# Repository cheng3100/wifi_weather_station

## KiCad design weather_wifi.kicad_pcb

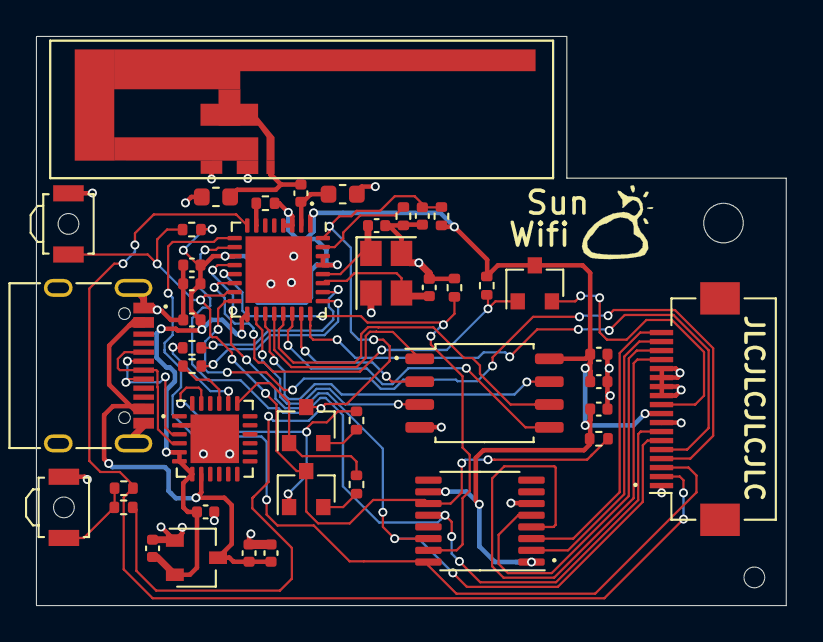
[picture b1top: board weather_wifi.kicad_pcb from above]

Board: 2 copper layers, 41.7 x 31.6 mm, 44 parts (0 on the bottom side), 41 nets.

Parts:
AE1: Antenna_pcb; antenna_trace_2.4g
C1, C5, C10, C13: 1uF; C_0402_1005Metric
C2, C3: 10pF; C_0402_1005Metric
C4: 10uF; C_0402_1005Metric
C6, C7, C8, C9, C11, C12: 0.1uF; C_0402_1005Metric
C14: 5.6pF; C_0402_1005Metric
G1: LOGO; pcb_girl
J1: FPC 1x18; Hirose_FH12-18S-0.5SH_1x18-1MP_P0.50mm_Horizontal
J2: USB2.0_type_c; USB_C_Receptacle_XKB_U262-16XN-4BVC11
L1, L2: DNP; L_0603_1608Metric
Q1, Q2: S8050; SOT-23
Q3: AO3401A; SOT-23
R1, R2, R3: 12K; R_0402_1005Metric
R4, R14: 47k; R_0402_1005Metric
R5, R6: 33; R_0402_1005Metric
R7: DNP; R_0402_1005Metric
R8, R10, R11, R12: 12k; R_0402_1005Metric
R13: 470; R_0402_1005Metric
SW1: key_reset/user; SW_SPST_B3U-3000P-B
SW2: key_flash; SW_SPST_B3U-3000P-B
U1: XC6206PxxxMR; SOT-23W
U2: ESP8266EX; QFN-32-1EP_5x5mm_P0.5mm_EP3.7x3.7mm
U3: W25Q32 4Mb flash; SOIC-8_5.23x5.23mm_P1.27mm
U4: CP2104; QFN-24-1EP_4x4mm_P0.5mm_EP2.7x2.7mm
U5: XPT2046TS; TSSOP-16_4.4x5mm_P0.65mm
Y1: 26Mhz; Crystal_SMD_3225-4Pin_3.2x2.5mm

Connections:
+3V3: C4.1, C5.1, C6.1, C7.1, C9.2, C10.1, C11.1, C12.1, J1.9, Q3.3, R4.1, R8.2, R10.2, R11.2, R14.2, U1.2, U2.1, U2.3, U2.4, U2.11, U2.17, U2.29, U2.30, U3.8, U4.5, U4.6, U4.7, U5.1, U5.10
/TFT_LEDA+: J1.10, Q3.2
/TFT_X+: J1.17, U5.2
/TFT_X-: J1.15, U5.4
/TFT_Y+: J1.18, U5.3
/TFT_Y-: J1.16, U5.5
/USB_DP+: J2.A6, J2.B6, U4.3
/USB_DP-: J2.A7, J2.B7, U4.4
DTR: Q2.1, R2.1, U4.23
GND: AE1.2, C1.2, C2.2, C3.2, C4.2, C5.2, C6.2, C7.2, C8.2, C9.1, C10.2, C11.2, C12.2, C13.2, J1.1, J1.8, J1.11, J1.12, J1.13, J1.14, J2.A1, J2.A12, J2.B1, J2.B12, J2.S1, L1.2, L2.2, R1.2, R12.2, SW1.2, SW2.2, U1.1, U2.33, U3.4, U4.2, U4.25, U5.6, Y1.2, Y1.4
LNA: C14.2, L1.1, U2.2
unnamed: AE1.1, C14.1, L2.1
unnamed: C2.1, U2.27, Y1.3
unnamed: C3.1, U2.28, Y1.1
unnamed: Q1.2, R2.2
unnamed: Q2.2, R3.2
unnamed: R1.1, U2.31
unnamed: R5.2, U4.21
unnamed: R6.2, U4.20
unnamed: R7.2, R13.2, SW1.1
RTS: Q1.1, R3.1, U4.19
VBUS: C1.1, C8.1, J2.A4, J2.A9, J2.B4, J2.B9, U1.3, U4.8
chip_en: R10.1, U2.7
gpio_0: Q2.3, R8.1, R14.1, SW2.1, U2.15, U5.11
gpio_2: Q3.1, R4.2, U2.14
gpio_4: J1.4, U2.16
gpio_5: J1.5, U2.24
gpio_12: J1.7, U2.10, U5.12
gpio_13: J1.6, U2.12, U5.14
gpio_14: J1.3, U2.9, U5.16
gpio_15: R12.1, U2.13, U5.15
gpio_16: J1.2, R7.1, U2.8
reset: C13.1, Q1.3, R11.1, R13.1, U2.32
sd_clk: U2.21, U3.6
sd_cs: U2.20, U3.1
sd_io0: U2.22, U3.5
sd_io1: U2.23, U3.2
sd_io2: U2.18, U3.3
sd_io3: U2.19, U3.7
u0rx: R5.1, U2.25
u0tx: R6.1, U2.26

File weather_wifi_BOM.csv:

Comment,Designator,Footprint,嘉立创元件编号
Antenna_pcb,AE1,weather_wifi:antenna_trace_2.4g,
1uF,"C1,C5,C10,C13",Capacitor_SMD:C_0402_1005Metric,C52923
6pF,C14,Capacitor_SMD:C_0402_1005Metric,C30274
10pF,"C2,C3",Capacitor_SMD:C_0402_1005Metric,C32949
10uF,C4,Capacitor_SMD:C_0402_1005Metric,C15525
0.1uF,"C6,C7,C8,C9,C11,C12",Capacitor_SMD:C_0402_1005Metric,C1546
FPC 1x18,J1,Connector_FFC-FPC:Hirose_FH12-18S-0.5SH_1x18-1MP_P0.50mm_Horizontal,
USB2.0_type_c,J2,Connector_USB:USB_C_Receptacle_XKB_U262-16XN-4BVC11,
DNP,"L1,L2",Inductor_SMD:L_0603_1608Metric,
S8050,"Q1,Q2",Package_TO_SOT_SMD:SOT-23,C2146
AO3401A,Q3,Package_TO_SOT_SMD:SOT-23,C15127
12K,"R1,R2,R3",Resistor_SMD:R_0402_1005Metric,C25752
470,R13,Resistor_SMD:R_0402_1005Metric,C25117
47k,"R4,R14",Resistor_SMD:R_0402_1005Metric,C25792
33,"R5,R6",Resistor_SMD:R_0402_1005Metric,C25105
DNP,R7,Resistor_SMD:R_0402_1005Metric,
12k,"R8,R10,R11,R12",Resistor_SMD:R_0402_1005Metric,C25752
key_reset/user,SW1,Button_Switch_SMD:SW_SPST_B3U-3000P-B,
key_flash,SW2,Button_Switch_SMD:SW_SPST_B3U-3000P-B,
XC6206PxxxMR,U1,Package_TO_SOT_SMD:SOT-23W,C5446
ESP8266EX,U2,Package_DFN_QFN:QFN-32-1EP_5x5mm_P0.5mm_EP3.7x3.7mm,
W25Q32 4Mb flash,U3,Package_SO:SOIC-8_5.23x5.23mm_P1.27mm,
CP2104,U4,Package_DFN_QFN:QFN-24-1EP_4x4mm_P0.5mm_EP2.7x2.7mm,C47742
XPT2046TS,U5,Package_SO:TSSOP-16_4.4x5mm_P0.65mm,
26Mhz,Y1,Crystal:Crystal_SMD_3225-4Pin_3.2x2.5mm,

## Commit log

2021-02-21 update for jlc manufacture
2021-02-22 Modify directory
